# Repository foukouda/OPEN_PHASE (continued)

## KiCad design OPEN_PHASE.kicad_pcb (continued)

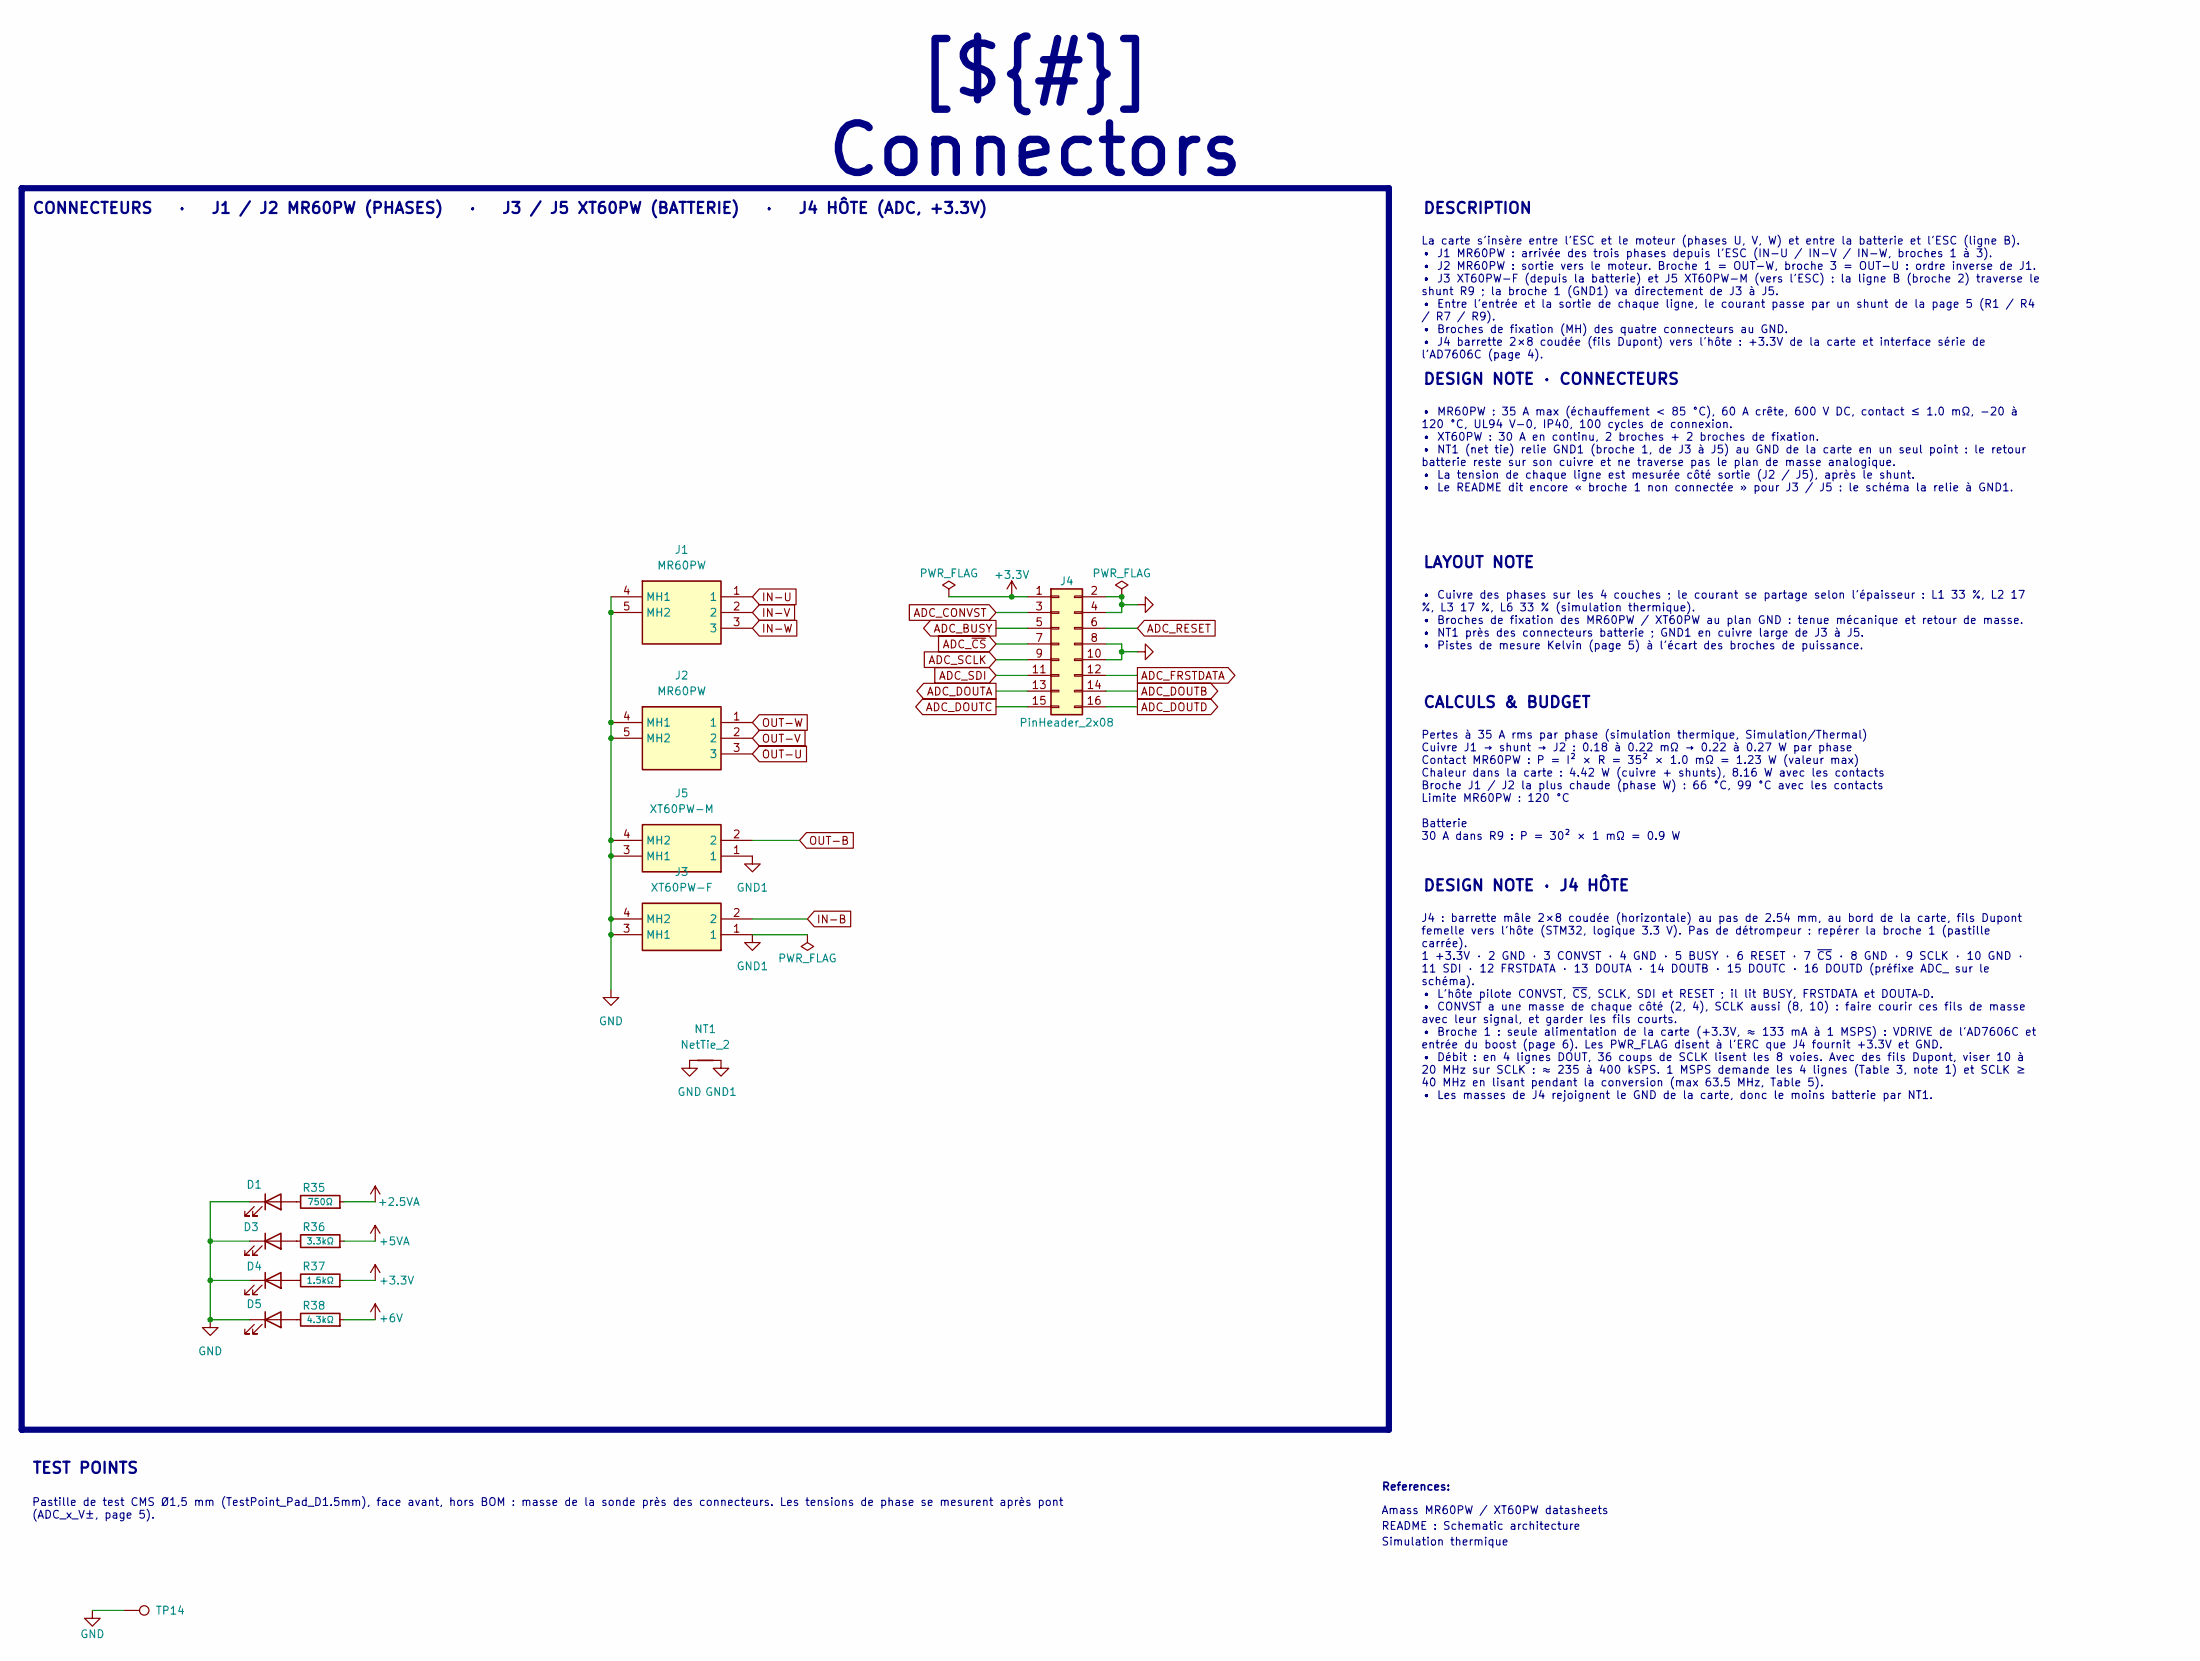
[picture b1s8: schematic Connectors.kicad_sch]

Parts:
D1, D3, D4, D5: LED; LED_0603_1608Metric; Manufacturer_Part_Number 150060RS75000
J1, J2: MR60PW; Manufacturer_Part_Number MR60PW
J3: XT60PW-F; AMASS_XT60PW-F_1x02_P7.20mm_Horizontal; Manufacturer_Part_Number XT60PW-F
J4: PinHeader_2x08; PinHeader_2x08_P2.54mm_Horizontal; Manufacturer_Part_Number 61301621021
J5: XT60PW-M; XT60PWM; Manufacturer_Part_Number XT60PW-M
NT1: NetTie_2; NetTie-2_SMD_Pad0.5mm
R35: 750Ω; R_0603_1608Metric; Manufacturer_Part_Number RC0603FR-07750RL
R36: 3.3kΩ; R_0603_1608Metric; Manufacturer_Part_Number RC0603FR-073K3L
R37: 1.5kΩ; R_0603_1608Metric; Manufacturer_Part_Number RC0603FR-071K5L
R38: 4.3kΩ; R_0603_1608Metric; Manufacturer_Part_Number RC0603FR-074K3L
TP14: TestPoint; TestPoint_Pad_D1.5mm

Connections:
+2.5VA: R35.2; also elsewhere on the board
+3.3V: J4.1, R37.2; also elsewhere on the board
+5VA: R36.2; also elsewhere on the board
+6V: R38.2; also elsewhere on the board
ADC_BUSY: J4.5; also elsewhere on the board
ADC_CONVST: J4.3; also elsewhere on the board
ADC_DOUTA: J4.13; also elsewhere on the board
ADC_DOUTB: J4.14; also elsewhere on the board
ADC_DOUTC: J4.15; also elsewhere on the board
ADC_DOUTD: J4.16; also elsewhere on the board
ADC_FRSTDATA: J4.12; also elsewhere on the board
ADC_RESET: J4.6; also elsewhere on the board
ADC_SCLK: J4.9; also elsewhere on the board
ADC_SDI: J4.11; also elsewhere on the board
ADC_~CS: J4.7; also elsewhere on the board
GND: D1.1 (K), D3.1 (K), D4.1 (K), D5.1 (K), J1.4 (MH1), J1.5 (MH2), J2.4 (MH1), J2.5 (MH2), J3.3 (MH1), J3.4 (MH2), J4.2, J4.4, J4.8, J4.10, J5.3 (MH1), J5.4 (MH2), NT1.1, TP14.1 (1_1); also elsewhere on the board
GND1: J3.1, J5.1, NT1.2
IN-B: J3.2; also elsewhere on the board
IN-U: J1.1; also elsewhere on the board
IN-V: J1.2; also elsewhere on the board
IN-W: J1.3; also elsewhere on the board
unnamed: D1.2 (A), R35.1
unnamed: D3.2 (A), R36.1
unnamed: D4.2 (A), R37.1
unnamed: D5.2 (A), R38.1
OUT-B: J5.2; also elsewhere on the board
OUT-U: J2.3; also elsewhere on the board
OUT-V: J2.2; also elsewhere on the board
OUT-W: J2.1; also elsewhere on the board

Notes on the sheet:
Amass MR60PW / XT60PW datasheets
References:
README : Schematic architecture
Simulation thermique
Pastille de test CMS Ø1,5 mm (TestPoint_Pad_D1.5mm), face avant, hors BOM : masse de la sonde près des connecteurs. Les tensions de phase se mesurent après pont (ADC_x_V±, page 5).
CALCULS & BUDGET
LAYOUT NOTE
DESCRIPTION
J4 : barrette mâle 2×8 coudée (horizontale) au pas de 2.54 mm, au bord de la carte, fils Dupont femelle vers l'hôte (STM32, logique 3.3 V). Pas de détrompeur : repérer la broche 1 (pastille carrée). 1 +3.3V · 2 GND · 3 CONVST · 4 GND · 5 BUSY · 6 RESET · 7 ~{CS} · 8 GND · 9 SCLK · 10 GND · 11 SDI ·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
TEST POINTS
[${#}] ${TITLE}
DESIGN NOTE · J4 HÔTE
• Cuivre des phases sur les 4 couches ; le courant se partage selon l'épaisseur : L1 33 %, L2 17 %, L3 17 %, L6 33 % (simulation thermique). • Broches de fixation des MR60PW / XT60PW au plan GND : tenue mécanique et retour de masse. • NT1 près des connecteurs batterie ; GND1 en cuivre large de J3 à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
Pertes à 35 A rms par phase (simulation thermique, Simulation/Thermal) Cuivre J1 → shunt → J2 : 0.18 à 0.22 mΩ → 0.22 à 0.27 W par phase Contact MR60PW : P = I² × R = 35² × 1.0 mΩ = 1.23 W (valeur max) Chaleur dans la carte : 4.42 W (cuivre + shunts), 8.16 W avec les contacts Broche J1 / J2 la plus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
La carte s'insère entre l'ESC et le moteur (phases U, V, W) et entre la batterie et l'ESC (ligne B). • J1 MR60PW : arrivée des trois phases depuis l'ESC (IN-U / IN-V / IN-W, broches 1 à 3). • J2 MR60PW : sortie vers le moteur. Broche 1 = OUT-W, broche 3 = OUT-U : ordre inverse de J1. • J3 XT60PW-F 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
DESIGN NOTE · CONNECTEURS
CONNECTEURS · J1 / J2 MR60PW (PHASES) · J3 / J5 XT60PW (BATTERIE) · J4 HÔTE (ADC, +3.3V)
• MR60PW : 35 A max (échauffement < 85 °C), 60 A crête, 600 V DC, contact ≤ 1.0 mΩ, −20 à 120 °C, UL94 V-0, IP40, 100 cycles de connexion. • XT60PW : 30 A en continu, 2 broches + 2 broches de fixation. • NT1 (net tie) relie GND1 (broche 1, de J3 à J5) au GND de la carte en un seul point : le retour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

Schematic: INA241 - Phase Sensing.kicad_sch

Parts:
C1, C2, C3, C17: 0.1µF; C_0603_1608Metric; Manufacturer_Part_Number GRM188R71H104KA93D
C5, C10, C16, C18: 1µF; C_0603_1608Metric; Manufacturer_Part_Number GRM188R71E105KA12D
C25, C29, C33, C42: 1nF C0G; C_0603_1608Metric; Manufacturer_Part_Number GRM1885C1H102JA01D
C31, C32, C34, C40: 180 pF C0G/NP0, 50 V, 0603; C_0603_1608Metric; Manufacturer_Part_Number GRM1885C1H181JA01D
IC2, IC4, IC6, IC10: INA241A4IDGKR; SOP65P490X110-8N; Manufacturer_Part_Number INA241A4IDGKR; Mouser Part Number 595-INA241A4IDGKR
R1, R4, R7, R9: PBV-R001-F1-0.5; PBVR001F110; Manufacturer_Part_Number PBV-R001-F1-0.5
R15, R20, R25, R30: 33Ω; R_0603_1608Metric; Manufacturer_Part_Number RC0603FR-0733RL
R16, R19, R21, R24, R26, R29, R31, R34: 9.1kΩ; R_0603_1608Metric; Manufacturer_Part_Number RC0603FR-079K1L
R17, R22, R27, R32: 40.2kΩ; R_0805_2012Metric; Manufacturer_Part_Number RC0805FR-0740K2L
R18, R23, R28, R33: 10kΩ; R_0805_2012Metric; Manufacturer_Part_Number RC0805FR-0710KL
Re1, Re2, Re3, Re4: 1kΩ; R_0603_1608Metric; Manufacturer_Part_Number RC0603FR-071KL
TP3, TP4, TP5, TP6, TP7, TP8: TestPoint; TestPoint_Pad_D1.5mm

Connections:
+2.5VA: IC2.3 (REF2), IC2.7 (REF1), IC4.3 (REF2), IC4.7 (REF1), IC6.3 (REF2), IC6.7 (REF1), IC10.3 (REF2), IC10.7 (REF1), TP7.1 (1_1); also elsewhere on the board
+5VA: C1.1, C2.1, C3.1, C5.1, C10.1, C16.1, C17.1, C18.1, IC2.6 (VS), IC4.6 (VS), IC6.6 (VS), IC10.6 (VS); also elsewhere on the board
ADC_BAT_I+: C42.1, R30.2; also elsewhere on the board
ADC_BAT_I-: C42.2, R31.2; also elsewhere on the board
ADC_BAT_V+: C40.1, Re4.2; also elsewhere on the board
ADC_BAT_V-: C40.2, R34.2; also elsewhere on the board
ADC_U_I+: C25.1, R15.2; also elsewhere on the board
ADC_U_I-: C25.2, R16.2; also elsewhere on the board
ADC_U_V+: C31.1, Re1.2; also elsewhere on the board
ADC_U_V-: C31.2, R19.2; also elsewhere on the board
ADC_V_I+: C29.1, R20.2; also elsewhere on the board
ADC_V_I-: C29.2, R21.2; also elsewhere on the board
ADC_V_V+: C32.1, Re2.2; also elsewhere on the board
ADC_V_V-: C32.2, R24.2; also elsewhere on the board
ADC_W_I+: C33.1, R25.2; also elsewhere on the board
ADC_W_I-: C33.2, R26.2; also elsewhere on the board
ADC_W_V+: C34.1, Re3.2; also elsewhere on the board
ADC_W_V-: C34.2, R29.2; also elsewhere on the board
GND: C1.2, C2.2, C3.2, C5.2, C10.2, C16.2, C17.2, C18.2, IC2.2 (GND), IC2.4 (NC), IC4.2 (GND), IC4.4 (NC), IC6.2 (GND), IC6.4 (NC), IC10.2 (GND), IC10.4 (NC), R16.1, R18.1, R19.1, R21.1, R23.1, R24.1, R26.1, R28.1, R29.1, R31.1, R33.1, R34.1, TP8.1 (1_1); also elsewhere on the board
IN-B: R9.1; also elsewhere on the board
IN-U: R1.1; also elsewhere on the board
IN-V: R4.1; also elsewhere on the board
IN-W: R7.1; also elsewhere on the board
INA_BAT: IC10.5 (OUT), R30.1, TP6.1 (1_1)
INA_U: IC2.5 (OUT), R15.1, TP3.1 (1_1)
INA_V: IC4.5 (OUT), R20.1, TP4.1 (1_1)
INA_W: IC6.5 (OUT), R25.1, TP5.1 (1_1)
unnamed: R17.2, R18.2, Re1.1
unnamed: R22.2, R23.2, Re2.1
unnamed: R27.2, R28.2, Re3.1
unnamed: R32.2, R33.2, Re4.1
OUT-B: R9.4, R32.1; also elsewhere on the board
OUT-U: R1.4, R17.1; also elsewhere on the board
OUT-V: R4.4, R22.1; also elsewhere on the board
OUT-W: R7.4, R27.1; also elsewhere on the board
SHUNT_BAT+: IC10.8 (IN+), R9.3
SHUNT_BAT-: IC10.1 (IN-), R9.2
SHUNT_U+: IC2.8 (IN+), R1.3
SHUNT_U-: IC2.1 (IN-), R1.2
SHUNT_V+: IC4.8 (IN+), R4.3
SHUNT_V-: IC4.1 (IN-), R4.2
SHUNT_W+: IC6.8 (IN+), R7.3
SHUNT_W-: IC6.1 (IN-), R7.2

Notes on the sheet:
ADC V6 courant · V5 tension
BATTERIE
Voie 3 · shunt R7 · IC6
README : Design review 3–8
Voie 4 · shunt R9 · IC10
References:
Voie 1 · shunt R1 · IC2
PHASE W
Voie 2 · shunt R4 · IC4
ADC V8 courant · V7 tension
ADC V4 courant · V3 tension
PHASE V
INA241A datasheet (SBOSA30D)
openEMS : inductance du shunt
PHASE U
Isabellenhütte PBV datasheet
ADC V2 courant · V1 tension
CALCULS & BUDGET
Mesure du courant des trois phases (U, V, W) et de la batterie (B), et de la tension des mêmes lignes. Le courant traverse un shunt 4 fils de 1 mΩ (R1 / R4 / R7 / R9, Isabellenhütte PBV). L'INA241A4 lit la tension entre les deux broches de mesure du shunt (Kelvin) et l'amplifie 100 fois autour du +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
• IN+ / IN− pris sur les broches de mesure 2 et 3 du shunt (Kelvin), pas sur le cuivre de puissance ; paire serrée jusqu'à l'INA241. • Boucle de mesure la plus petite possible : 1 nH vaut R = 1 mΩ à 160 kHz. • C17/C18 au plus près de VS / GND. Filtres près des entrées de l'AD7606C. • Shunt : 1.2 W 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
FILTRES · VOIES COURANT
TEST POINTS
Pastilles de test CMS Ø1,5 mm (TestPoint_Pad_D1.5mm), face avant, hors BOM. Sorties INA241 avant le filtre RC vers l'ADC ; à 0 A elles valent +2.5VA (REF1 = REF2).
DESCRIPTION
DESIGN NOTE · VOIES VERS L'AD7606C
INA241A4 + SHUNT 1 mΩ · 4 VOIES : U, V, W, BATTERIE
• Courant : R15 33 Ω isole la sortie de l'INA241 de la capacité. Filtre différentiel : C25 1 nF C0G entre V+ et V−, V− à la masse par R16 9.1 kΩ → 17.5 kHz. • R16 et le courant d'entrée de l'ADC donnent 15 mV d'offset (≈ 0.75 A) : calibration du zéro ; ne pas réduire R16 sans recalculer le filtre (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
LAYOUT NOTE
INA241A1 : 10 V/V INA241A2 : 20 V/V INA241A3 : 50 V/V INA241A4 : 100 V/V (monté) INA241A5 : 200 V/V • Avec 1 mΩ et 100 V/V : 100 mV/A, saturation vers ±23 A. Version petits moteurs (1205.5 en 1S, pointes vers 18 A) ; A2 (20 V/V, ±115 A) pour les gros moteurs. • REF1 = REF2 = +2.5VA : zéro au milieu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
Voie courant (×4) V = 2.5 V − G × Rs × I = 2.5 V − 100 V/V × 1 mΩ × I = 2.5 V − 100 mV/A × I 18 A → ±1.8 V ; saturation vers ±23 A fc = 1 / (2π × R16 × C25) = 1 / (2π × 9.1 kΩ × 1 nF) = 17.5 kHz Offset : I(V−) = (0 − 2 V) / 1.2 MΩ = −1.7 µA → V− = 1.7 µA × 9.1 kΩ = 15 mV ≈ 0.15 A Shunt : P = I² × R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
[${#}] ${TITLE}
DESIGN NOTE · GAIN ET SHUNT

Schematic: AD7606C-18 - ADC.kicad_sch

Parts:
C20, C21, C35, C38, C41: 100nF; C_0603_1608Metric; Manufacturer_Part_Number GRM188R71H104KA93D
C36, C37: 1uF; C_0603_1608Metric; Manufacturer_Part_Number GRM188R71E105KA12D
C39: 10µF; C_0805_2012Metric_4T; Manufacturer_Part_Number CL21B106KOQNNNE
IC1: AD7606C-18BSTZ; QFP50P1200X1200X160-64N; Manufacturer_Part_Number AD7606C-18BSTZ; Mouser Part Number 584-AD7606C-18BSTZ
R39, R40, R41: 100Ω; R_0603_1608Metric; Manufacturer_Part_Number RC0603FR-07100RL
R42, R43, R44: 100kΩ; R_0603_1608Metric; Manufacturer_Part_Number RC0603FR-07100KL
RN1, RN2: RP_100Ω; R_Array_Concave_4x0603; Manufacturer_Part_Number CAT16-101J4LF
TP1, TP2, TP15, TP16: TestPoint; TestPoint_Pad_D1.5mm

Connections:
+2.5VA: C41.2, IC1.42 (REFIN/REFOUT), TP1.1 (1_1); also elsewhere on the board
+3.3V: C21.2, IC1.3 (OS_0), IC1.4 (OS_1), IC1.5 (OS_2), IC1.6 (~PAR/SER_SEL), IC1.7 (~STBY), IC1.8 (RANGE), IC1.10 (~WR), IC1.23 (VDRIVE), R42.1; also elsewhere on the board
+5VA: C20.1, C35.2, C38.2, IC1.1 (AVCC_1), IC1.37 (AVCC_2), IC1.38 (AVCC_3), IC1.48 (AVCC_4); also elsewhere on the board
/Project Architecture/AD7606C-18_ADC/BUSY: IC1.14 (BUSY), RN1.4 (R4.1), TP16.1 (1_1)
/Project Architecture/AD7606C-18_ADC/CONVST: IC1.9 (CONVST), R39.1, R43.1, TP15.1 (1_1)
/Project Architecture/AD7606C-18_ADC/DOUTA: IC1.24 (DB9/DOUTA), RN2.4 (R4.1)
/Project Architecture/AD7606C-18_ADC/DOUTB: IC1.25 (DB10/DOUTB), RN2.3 (R3.1)
/Project Architecture/AD7606C-18_ADC/DOUTC: IC1.27 (DB11/DOUTC), RN2.2 (R2.1)
/Project Architecture/AD7606C-18_ADC/DOUTD: IC1.28 (DB12/DOUTD), RN2.1 (R1.1)
/Project Architecture/AD7606C-18_ADC/FRSTDATA: IC1.15 (FRSTDATA), RN1.1 (R1.1)
/Project Architecture/AD7606C-18_ADC/RESET: IC1.11 (RESET), R40.1, R44.1
/Project Architecture/AD7606C-18_ADC/SCLK: IC1.12 (~RD/SCLK), RN1.2 (R2.1)
/Project Architecture/AD7606C-18_ADC/SDI: IC1.29 (DB13/SDI), R41.1
/Project Architecture/AD7606C-18_ADC/~CS: IC1.13 (~CS), R42.2, RN1.3 (R3.1)
ADC_BAT_I+: IC1.51 (V2+); also elsewhere on the board
ADC_BAT_I-: IC1.52 (V2-); also elsewhere on the board
ADC_BAT_V+: IC1.49 (V1+); also elsewhere on the board
ADC_BAT_V-: IC1.50 (V1-); also elsewhere on the board
ADC_BUSY: RN1.5 (R4.2); also elsewhere on the board
ADC_CONVST: R39.2; also elsewhere on the board
ADC_DOUTA: RN2.5 (R4.2); also elsewhere on the board
ADC_DOUTB: RN2.6 (R3.2); also elsewhere on the board
ADC_DOUTC: RN2.7 (R2.2); also elsewhere on the board
ADC_DOUTD: RN2.8 (R1.2); also elsewhere on the board
ADC_FRSTDATA: RN1.8 (R1.2); also elsewhere on the board
ADC_RESET: R40.2; also elsewhere on the board
ADC_SCLK: RN1.7 (R2.2); also elsewhere on the board
ADC_SDI: R41.2; also elsewhere on the board
ADC_U_I+: IC1.63 (V8+); also elsewhere on the board
ADC_U_I-: IC1.64 (V8-); also elsewhere on the board
ADC_U_V+: IC1.61 (V7+); also elsewhere on the board
ADC_U_V-: IC1.62 (V7-); also elsewhere on the board
ADC_V_I+: IC1.59 (V6+); also elsewhere on the board
ADC_V_I-: IC1.60 (V6-); also elsewhere on the board
ADC_V_V+: IC1.57 (V5+); also elsewhere on the board
ADC_V_V-: IC1.58 (V5-); also elsewhere on the board
ADC_W_I+: IC1.55 (V4+); also elsewhere on the board
ADC_W_I-: IC1.56 (V4-); also elsewhere on the board
ADC_W_V+: IC1.53 (V3+); also elsewhere on the board
ADC_W_V-: IC1.54 (V3-); also elsewhere on the board
ADC_~CS: RN1.6 (R3.2); also elsewhere on the board
GND: C20.2, C21.1, C35.1, C36.2, C37.2, C38.1, C39.1, C39.4, C41.1, IC1.2 (AGND_1), IC1.16 (DB2), IC1.17 (DB3), IC1.18 (DB4), IC1.26 (AGND_2), IC1.30 (DB14), IC1.31 (DB15), IC1.32 (DB16/DB0), IC1.33 (DB17/DB1), IC1.34 (REF_SELECT), IC1.35 (AGND_3), IC1.40 (AGND_4), IC1.41 (AGND_5), IC1.43 (REFGND_1), IC1.46 (REFGND_2), IC1.47 (AGND_6), R43.2, R44.2, TP2.1 (1_1); also elsewhere on the board
unnamed: C39.2, C39.3, IC1.44 (REFCAPA), IC1.45 (REFCAPB)
unnamed: C37.1, IC1.36 (REGCAP_1)
unnamed: C36.1, IC1.39 (REGCAP_2)

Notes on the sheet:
References:
J. Pieper ADC investigation
STM32G474 Datasheet p.81
AN5346
AD7606C-18 datasheet (Rev. B)
DESCRIPTION
Pastilles de test CMS Ø1,5 mm (TestPoint_Pad_D1.5mm), face avant, hors BOM. REFIN (+2.5VA) au plus près de l'AD7606C. TP15 (CONVST) et TP16 (BUSY), côté AD7606C (avant les 100 Ω série) : début et fin de conversion, pour déclencher l'oscilloscope.
V1 : tension batterie (ADC_BAT_V±) V2 : courant batterie (ADC_BAT_I±) V3 : tension phase W (ADC_W_V±) V4 : courant phase W (ADC_W_I±) V5 : tension phase V (ADC_V_V±) V6 : courant phase V (ADC_V_I±) V7 : tension phase U (ADC_U_V±) V8 : courant phase U (ADC_U_I±) • Courant et tension d'une même ligne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
Plage ±5 V différentielle (mode logiciel) 1 LSB = 10 V / 2^18 = 38.1 µV Courant : 38.1 µV / 100 mV/A = 0.38 mA par LSB ; 18 A = ±1.8 V = 36 % de la plage Tension : 38.1 µV / 0.1977 = 0.19 mV par LSB ; 5 V / 0.1977 = 25.3 V max (6S chargée : 25.2 V → 4.98 V, juste sous la limite) Entrées RIN = 1.2 M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
CALCULS & BUDGET
• Plan de masse plein sous l'AD7606C, sans séparation analogique / numérique (datasheet). • Un via (ou plusieurs) par broche de masse, jamais un via partagé. • C39, C36/C37, C41 et les 100 nF d'AVCC collés à leurs broches. • Aucune piste numérique sous le boîtier ; CONVST et les horloges entourées 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
DESIGN NOTE · CANAUX
LAYOUT NOTE
[${#}] ${TITLE}
DESIGN NOTE · RÉFÉRENCE, DÉCOUPLAGE, CONFIGURATION
TEST POINTS
• REFIN/REFOUT = +2.5VA, C41 100 nF. REF SELECT doit être à 0 pour prendre cette référence externe (à 1 : référence interne). • REFCAPA + REFCAPB reliés, C39 10 µF faible ESR (tampon de référence à 4.4 V). • REGCAP : C36 et C37 1 µF chacun, séparément (LDO internes 1.9 V). • AVCC : C20, C35, C38 10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
IC1 AD7606C-18 : ADC 8 voies, 18 bits, 1 MSPS, échantillonnage simultané. Les 8 entrées différentielles reçoivent les 4 courants (sorties INA241 filtrées) et les 4 tensions (ponts 40.2 kΩ / 10 kΩ) de la page 5. Pourquoi cet ADC : les 8 voies sont prises au même instant (front montant de CONVST), do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
AD7606C-18 · ADC 8 VOIES SIMULTANÉES, 18 BITS, 1 MSPS

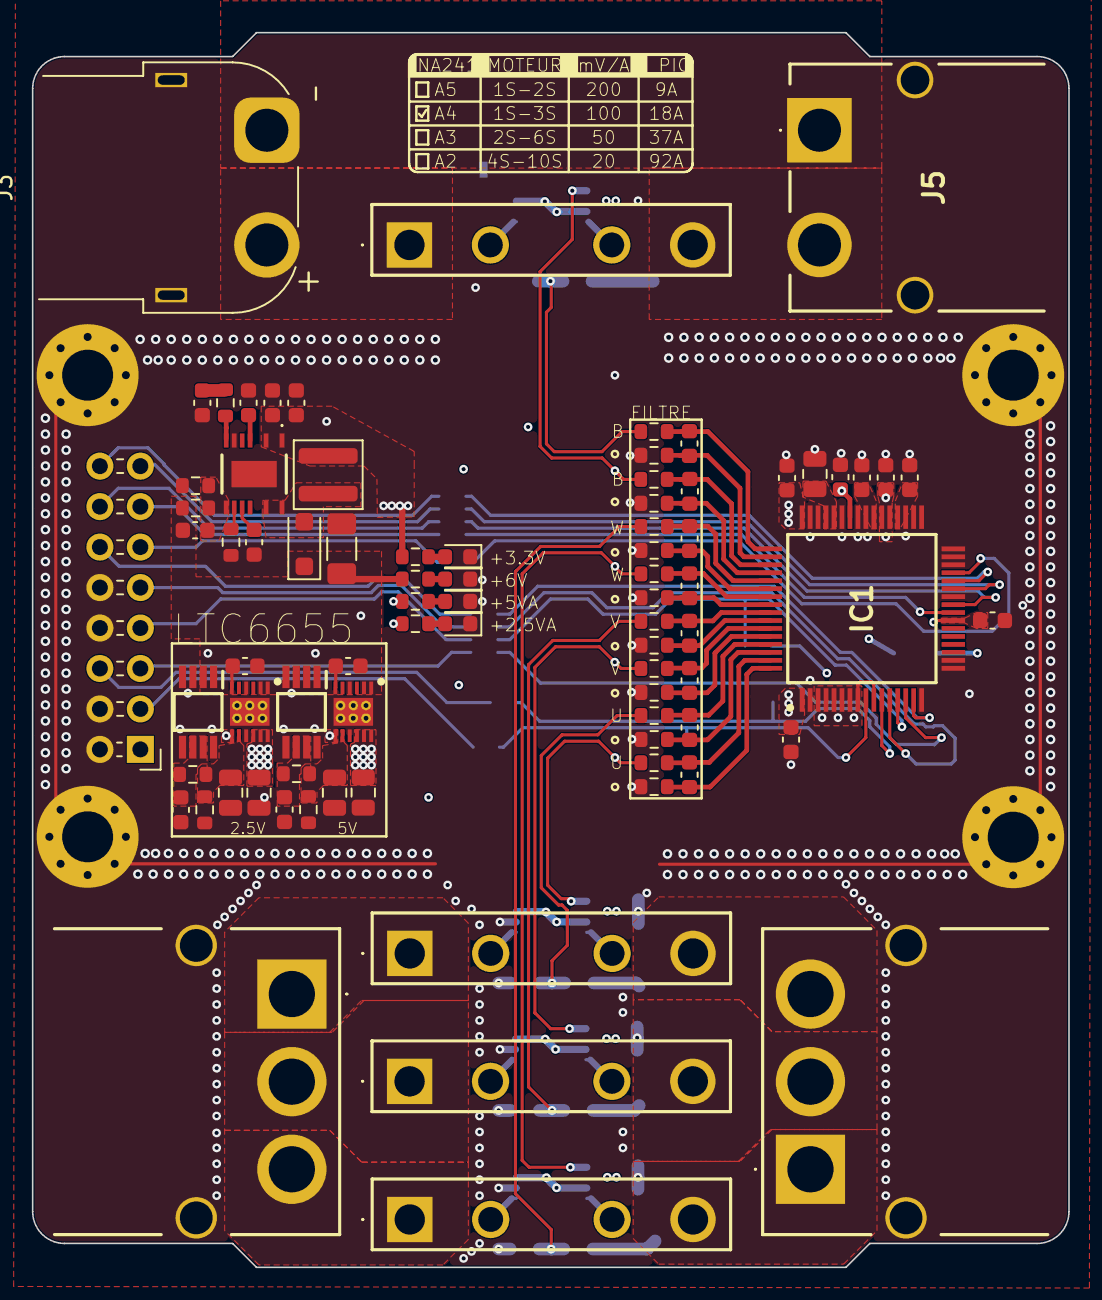
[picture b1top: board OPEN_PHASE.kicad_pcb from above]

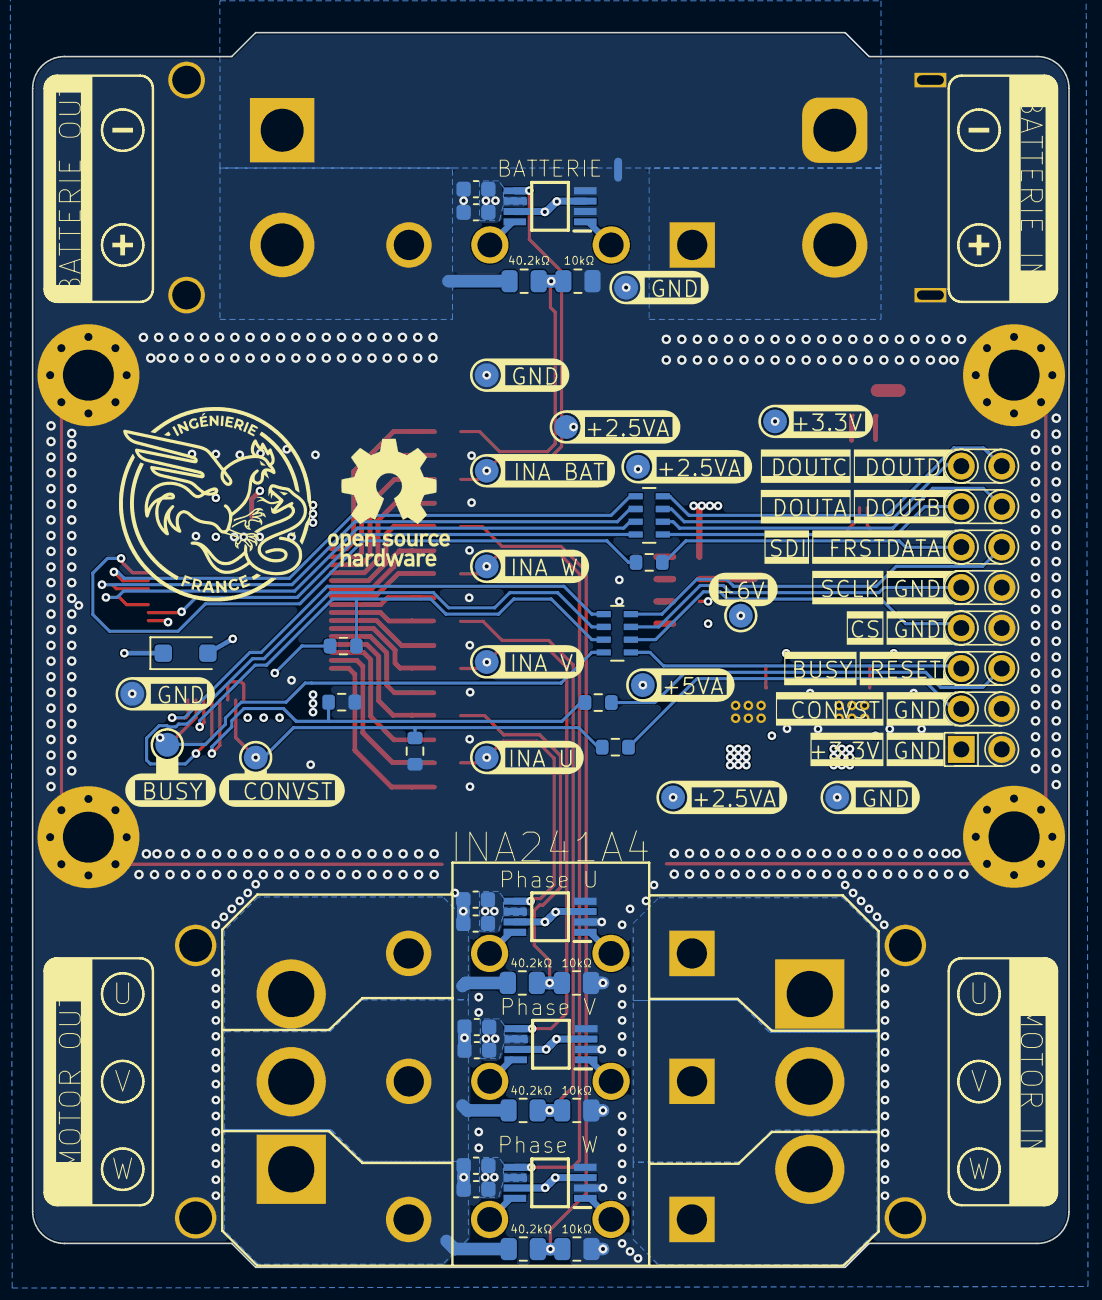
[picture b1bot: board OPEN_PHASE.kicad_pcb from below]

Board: 4 copper layers, 65.0 x 77.5 mm, 131 parts (47 on the bottom side), 86 nets.

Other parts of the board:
LOGO2: OSHW-Logo_7.5x8mm_SilkScreen

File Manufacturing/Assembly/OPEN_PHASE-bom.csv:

Row,Quantity Per PCB,References,Value,Datasheet,Footprint,Description,Manufacturer_Name,Manufacturer_Part_Number,Supplier Part Number
1,1,C28,"4,7 pF C0G 0603",,C_0603_1608Metric,Unpolarized capacitor,Yageo,CC0603CRNPO9BN4R7,
2,4,C31 C32 C34 C40,"180 pF C0G/NP0, 50 V, 0603",,C_0603_1608Metric,Unpolarized capacitor,Murata,GRM1885C1H181JA01D,
3,4,C25 C29 C33 C42,1nF C0G,,C_0603_1608Metric,Unpolarized capacitor,Murata,GRM1885C1H102JA01D,
4,1,C26,1 nF X7R 0603,,C_0603_1608Metric,Unpolarized capacitor,Murata,GRM188R71H102KA01D,
5,1,C24,10 nF X7R 0603,,C_0603_1608Metric,Unpolarized capacitor,Murata,GRM188R71H103KA01D,
6,10,C1 C2 C3 C17 C20 C21 C23 C35 C38 C41,0.1µF,,C_0603_1608Metric,Unpolarized capacitor,Murata,GRM188R71H104KA93D,
7,7,C5 C10 C16 C18 C27 C36 C37,1µF,,C_0603_1608Metric,Unpolarized capacitor,Murata,GRM188R71E105KA12D,
8,3,C9 C11 C22,4.7µF,,C_0603_1608Metric,Unpolarized capacitor,Murata,GRM188R61E475KE11D,
9,2,C8 C12,10µF,,C_0603_1608Metric,Unpolarized capacitor,Samsung Electro-Mechanics,CL10A106KO8NQNC,
10,5,C13 C14 C15 C19 C39,10µF,,C_0805_2012Metric,Unpolarized capacitor,Samsung Electro-Mechanics,CL21B106KOQNNNE,
11,1,C30,22 µF X7R 1206,,C_1206_3216Metric_Pad1.33x1.80mm_HandSolder,Unpolarized capacitor,Murata,GRM31CZ71C226ME15L,
12,4,D1 D3 D4 D5,LED,,LED_0603_1608Metric,Light emitting diode,Wurth Elektronik,150060RS75000,
13,2,D2 D6,PMEG2020EH,https://assets.nexperia.com/documents/data-sheet/PMEG2020EH_EJ.pdf,D_SOD-123F,"20V, 2A very low Vf MEGA Schottky barrier rectifier, SOD-123F",Nexperia,"PMEG2020EH,115",
14,1,IC1,AD7606C-18BSTZ,https://www.analog.com/media/en/technical-documentation/data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,QFP50P1200X1200X160-64N,"Analog to Digital Converters - ADC 8-ch DAS w/18-bit, bipola",Analog Devices,AD7606C-18BSTZ,
15,4,IC2 IC4 IC6 IC10,INA241A4IDGKR,https://www.ti.com/lit/ds/symlink/ina241a.pdf?ts=16986485827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,SOP65P490X110-8N,Current Sense Amplifier 1 Circuit Single-Ended 8-VSSOP,Texas Instruments,INA241A4IDGKR,
16,2,IC8 IC9,LT3045EDD-1#TRPBF,http://www.linear.com/docs/57863,SON45P300X300X80-13N-D,"LDO Voltage Regulators 20V, 500mA, Ultralow N, Ultrahigh PSRR L",Analog Devices,LT3045EDD-1#TRPBF,
17,1,IC5,LT8362EMSE#PBF,https://www.analog.com/media/en/technical-documentation/data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,LT8362EMSEPBF,"Switching Voltage Regulators L IQ Boost/SEPIC/Inv Conv w/ 2A, 60V Swi",Analog Devices,LT8362EMSE#PBF,
18,1,IC3,LTC6655BHMS8-2.5#PBF,https://www.analog.com/media/en/technical-documentation/data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,SOP65P490X110-8N,"0.25PPM N, L DRIFT PREC REFS",Analog Devices,LTC6655BHMS8-2.5#PBF,
19,1,IC7,LTC6655BHMS8-5#PBF,http://www.analog.com/media/en/technical-documentation/data-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,SOP65P490X110-8N,"Voltage References Ultra Low Noise, 5V Precision Voltage Reference",Analog Devices,LTC6655BHMS8-5#PBF,
20,2,J1 J2,MR60PW,https://www.tme.eu/Document/fd4b3517709a946d7b01cf4810656931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,MR60PW,Connector: DC supply; socket; MR60; male; PIN: 3; on PCBs; THT; black,Amass,MR60PW,
21,1,J4,PinHeader_2x08,~,PinHeader_2x08_P2.54mm_Horizontal,"Pin header, 2x08, 2.54 mm, horizontal (right angle), for Dupont jumper wires (odd pins row 1, even pins row 2). Host interface of the AD7606C-18 and +3.3V input",Wurth Elektronik,61301621021,
22,1,J3,XT60PW-F,https://www.tme.eu/Document/1191bc2fa3aee3c446e5a895fd8f7983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,AMASS_XT60PW-F_1x02_P7.20mm_Horizontal,Connector: DC supply; socket; XT60; female; PIN: 2; on PCBs; THT; 30A,Amass,XT60PW-F,
23,1,J5,XT60PW-M,https://www.tme.eu/Document/b13629717d44ae038681dba08d18c0b6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,XT60PWM,Connector: DC supply; socket; XT60; male; PIN: 2; on PCBs; THT; 30A,Amass,XT60PW-M,
24,1,L1,74438357022,https://www.we-online.com/components/products/datasheet/7443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,L_Wuerth_MAPI-4030,"WE-MAPI SMT Power Inductor Size 4030; L = 2,2 µH; IRP,40K = 7,1 A; Isat,10% = 4,6 A; Isat,30% = 9,2 A; RDC = 22 mΩ typ / 26 mΩ max",Wurth Elektronik,74438357022,
25,4,R15 R20 R25 R30,33Ω,,R_0603_1608Metric,Resistor,Yageo,RC0603FR-0733RL,
26,3,R39 R40 R41,100Ω,,R_0603_1608Metric,Resistor,Yageo,RC0603FR-07100RL,
27,1,R35,750Ω,,R_0603_1608Metric,Resistor,Yageo,RC0603FR-07750RL,
28,6,R8 R11 Re1 Re2 Re3 Re4,1kΩ,,R_0603_1608Metric,Resistor,Yageo,RC0603FR-071KL,
29,1,R37,1.5kΩ,,R_0603_1608Metric,Resistor,Yageo,RC0603FR-071K5L,
30,1,R36,3.3kΩ,,R_0603_1608Metric,Resistor,Yageo,RC0603FR-073K3L,
31,1,R38,4.3kΩ,,R_0603_1608Metric,Resistor,Yageo,RC0603FR-074K3L,
32,8,R16 R19 R21 R24 R26 R29 R31 R34,9.1kΩ,,R_0603_1608Metric,Resistor,Yageo,RC0603FR-079K1L,
33,4,R18 R23 R28 R33,10kΩ,,R_0805_2012Metric,Resistor,Yageo,RC0805FR-0710KL,
34,1,R2,20kΩ,,R_0603_1608Metric,Resistor,Yageo,RC0603FR-0720KL,
35,1,R12,24.9kΩ,,R_0603_1608Metric,Resistor,Yageo,RC0603FR-0724K9L,
36,4,R17 R22 R27 R32,40.2kΩ,,R_0805_2012Metric,Resistor,Yageo,RC0805FR-0740K2L,
37,1,R14,49.9kΩ,,R_0603_1608Metric,Resistor,Yageo,RC0603FR-0749K9L,
38,3,R42 R43 R44,100kΩ,,R_0603_1608Metric,Resistor,Yageo,RC0603FR-07100KL,
39,1,R3,"36,5kΩ",,R_0603_1608Metric,Resistor,Yageo,RC0603FR-0736K5L,
40,1,R6,365kΩ,,R_0603_1608Metric,Resistor,Yageo,RC0603FR-07365KL,
41,1,R5,1MΩ,,R_0603_1608Metric,Resistor,Yageo,RC0603FR-071ML,
42,4,R1 R4 R7 R9,PBV-R001-F1-1.0,https://cms.nacsemi.com/content/AuthDatasheets/Isabellehuett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,PBVR001F110,"ISA-PLAN // Precision resistors Metal Film Resistor, 1 m, 3 W, +/-1 %",Isabellenhutte,PBV-R001-F1-1.0,
43,2,RN1 RN2,RP_100Ω,,R_Array_Concave_4x0603,"4 resistor network, parallel topology",Bourns,CAT16-101J4LF,
